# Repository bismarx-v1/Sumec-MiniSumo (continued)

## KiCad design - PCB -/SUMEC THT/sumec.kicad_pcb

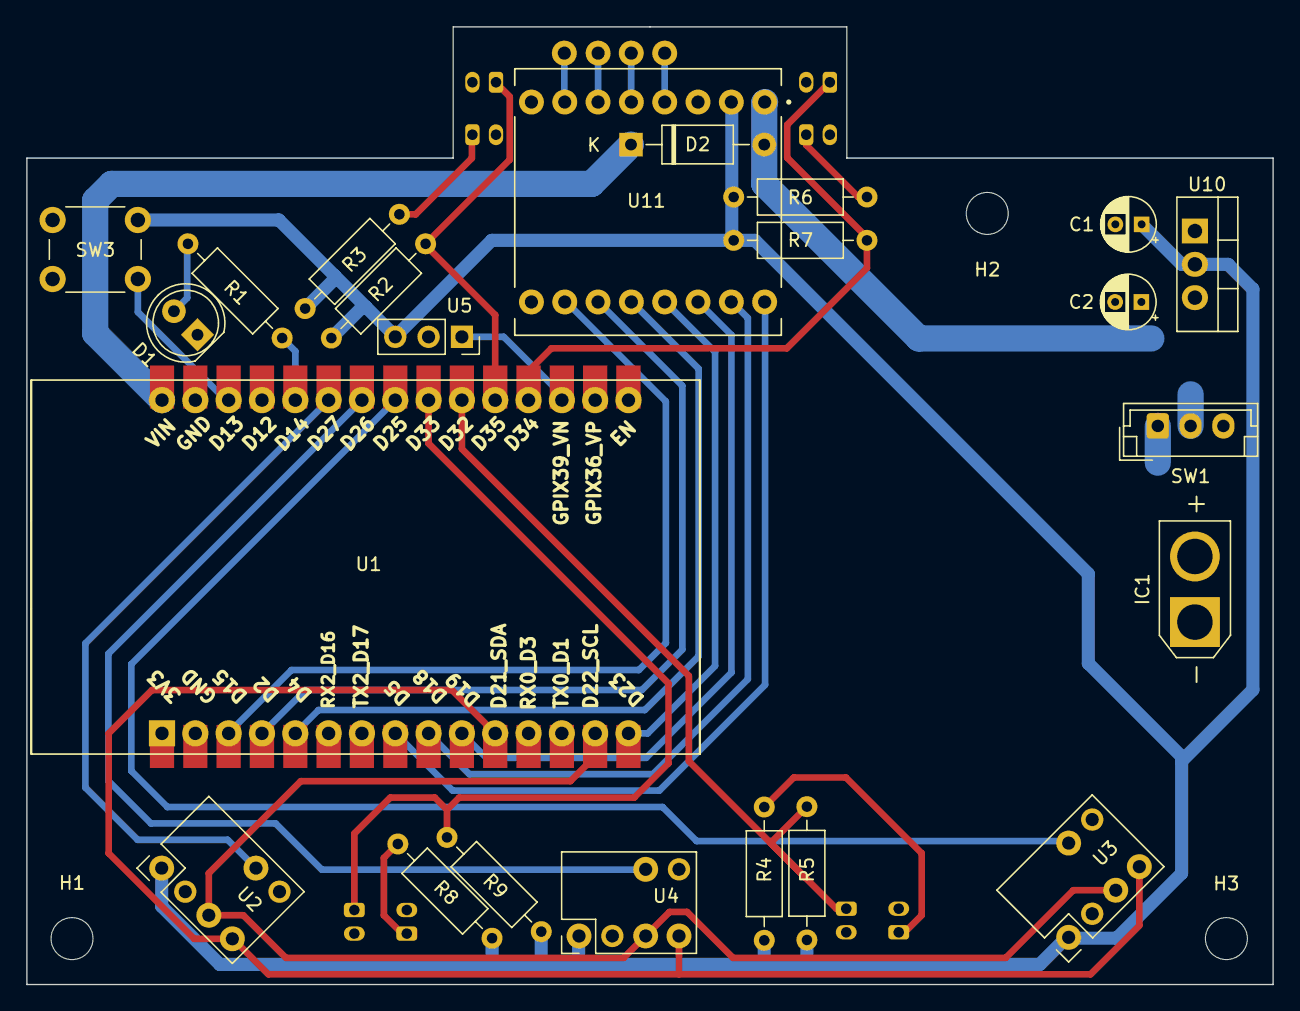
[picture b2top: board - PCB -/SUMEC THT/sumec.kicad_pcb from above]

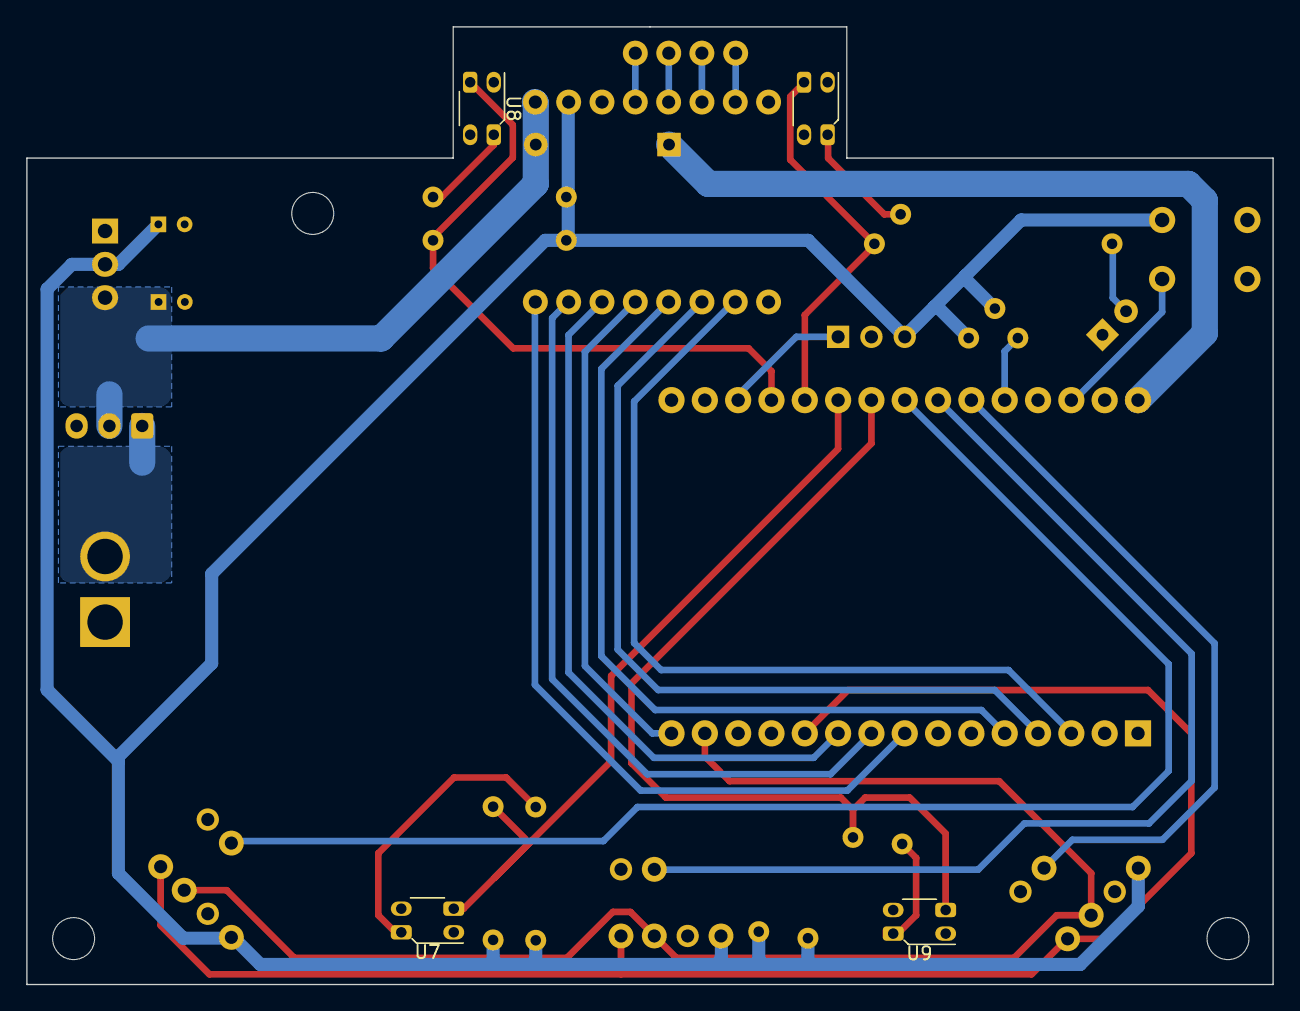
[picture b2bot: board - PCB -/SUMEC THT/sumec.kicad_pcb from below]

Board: 2 copper layers, 95.0 x 73.0 mm, 34 parts (4 on the bottom side), 33 nets.

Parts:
C1, C2: 10uF; CP_Radial_D4.0mm_P2.00mm
D1: RLED; LED_D5.0mm
D2: D_Schottky; D_A-405_P10.16mm_Horizontal
H1, H2, H3: MountingHole M3; MountingHole_3.2mm_M3
IC1: XT30U-F; AMASS_XT30U-M_1x02_P5.0mm_Vertical
J1, J2, J3, J4: Conn_01x01_Pin; SolderWire-0.5sqmm_1x01_D0.9mm_OD2.3mm
R1: 75; R_Axial_DIN0207_L6.3mm_D2.5mm_P10.16mm_Horizontal
R2, R4, R6, R8: 100; R_Axial_DIN0207_L6.3mm_D2.5mm_P10.16mm_Horizontal
R3, R5, R7, R9: 10k; R_Axial_DIN0207_L6.3mm_D2.5mm_P10.16mm_Horizontal
SW1: SW_SPDT; JST_EH_B3B-EH-A_1x03_P2.50mm_Vertical
SW3: SW_Push; SW_PUSH_6mm
U1: ESP32-DEVKIT-V1; MODULE_ESP32_DEVKIT_V1 B_Cu - PADS and no mount holes
U2, U3, U4: VL53L0X; GY-530 VL53L0X
U5: TSOP382xx; PinSocket_1x03_P2.54mm_Vertical
U6, U7, U8, U9: QRE1113; OnSemi_CASE100AQ - QRE1113
U10: LD1117AV33; TO-220-3_Vertical
U11: ROB-14450; ROB-14450 - TB6612FNG (MOTOR DRIVER)

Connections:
12V IN: IC1.2, SW1.1 (A)
+3V3: C1.1, R2.2, R3.1, R4.2, R5.1, R6.2, R7.1, R8.2, R9.1, SW3.1, U2.1 (VIN), U3.1 (VIN), U4.1 (VIN), U5.3 (Vs), U10.2 (OUT), U11.2 (VCC)
+12V: C2.1, D2.2 (A), SW1.2 (B), U10.3 (IN), U11.1 (VM)
AI1: U1.10 (D19), U11.14 (AI1)
AI2: U1.9 (D18), U11.15 (AI2)
BI1: U1.5 (D4), U11.12 (BI1)
BI2: U1.4 (D2), U11.11 (BI2)
GND: C1.2, C2.2, D1.1 (K), IC1.1, U1.2 (GND), U1.29 (GND), U2.2 (GND), U3.2 (GND), U4.2 (GND), U5.2 (GND), U6.2 (K), U6.4, U7.2 (K), U7.4, U8.2 (K), U8.4, U9.2 (K), U9.4, U10.1 (ADJ/GND), U11.3 (GND), U11.8 (GND), U11.9 (GND)
IR MODULE: U1.18 (GPIX39_VN), U5.1 (OUT)
LED SIGNALISATION: R1.2, U1.26 (D14)
MOTOR 1 +: J1.1, U11.4 (A01)
MOTOR 1 -: J2.1, U11.5 (A02)
MOTOR 2 +: J4.1, U11.6 (B02)
MOTOR 2 -: J3.1, U11.7 (B01)
unnamed: D1.2 (A), R1.1
unnamed: D2.1 (K), U1.30 (VIN)
unnamed: R2.1, U6.1 (A)
unnamed: R4.1, U7.1 (A)
unnamed: R6.1, U8.1 (A)
unnamed: R8.1, U9.1 (A)
PWMA: U1.8 (D5), U11.16 (PWMA)
PWMB: U1.3 (D15), U11.10 (PWMB)
QRE1113 A: R3.2, U1.20 (D35), U6.3
QRE1113 B: R5.2, U1.21 (D32), U7.3
QRE1113 C: R7.2, U1.19 (D34), U8.3
QRE1113 D: R9.2, U1.22 (D33), U9.3
SCL: U1.14 (D22_SCL), U2.3 (SCL), U3.3 (SCL), U4.3 (SCL)
SDA: U1.11 (D21_SDA), U2.4 (SDA), U3.4 (SDA), U4.4 (SDA)
STBY: U1.15 (D23), U11.13 (STBY)
TEST PROGRAM: SW3.2, U1.28 (D13)
X-SHUT 1: U1.25 (D27), U2.6 (XSHUT)
X-SHUT 2: U1.23 (D25), U3.6 (XSHUT)
X-SHUT 3: U1.24 (D26), U4.6 (XSHUT)

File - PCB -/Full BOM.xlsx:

| QTY | VALUE | COMPONENT | COST | DO WE HAVE IT?
 | 2 | 10uF | Cappacitor |  | 9
 | 1 | RED | LED | 0 | YES
 | 1 | D_Schottky | Diode |  | 2
 | 3 | M3 | Mounting Hole |  | 30
 | 1 | XT30U-F | Battery conneector |  | 2F and 2M
 | 1 | 75 | Resistor
 | 4 | 100 | Resistor |  | 6
 | 4 | 10k | Resistor |  | 10
 | 1 | SW_SPDT | Switch (3 pin header) |  | 2 types 8 in total
 | 1 | SW_Push | Button | 0 | YES
 | 1 | ESP32-DEVKIT-V1 | MCU |  | 3
 | 3 | VL53L0X | Laser Sensor |  | 4
 | 1 | TSOP382xx | IR Sensor |  | 1 module,
 | 4 | QRE1113 | Line Rensor |  | 10 smd 11 thd
 | 1 | LD1117AV33 | Stabiliastor |  | 2
 | 1 | ROB-14450 | Motor Driver |  | 4+1
 | 15x2 | 2,54mm | Pin Header
 | 8x2 | 2,54mm | Pin Header
 | 3 | CUSTOM MADE | Laser sensor connector
 | 2 | 12V 150/300/500 RPM | DC Motors |  | 8
 | 1 | 450mAh, 12,6V full charge | Battery/Terrorist battery |  | 1+1
 | 2 | JSUMO | Silicon wheels |  | 3
 | 2 | JSUMO/Custom made | Aluminuim wheels |  | 2+2
 | 1 | Tester | Battery Tester |  | 1

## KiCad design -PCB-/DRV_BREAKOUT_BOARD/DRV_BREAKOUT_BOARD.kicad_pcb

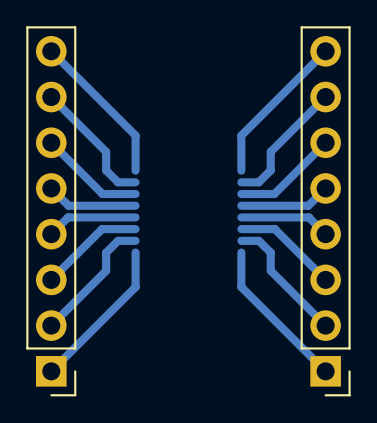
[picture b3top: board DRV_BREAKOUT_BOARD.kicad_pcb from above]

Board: 2 copper layers, 3 parts (1 on the bottom side), 16 nets.

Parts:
IC1: DRV8874PWPR; DRV8874
J1, J2: Conn_01x08_Pin; PinHeader_1x08_P2.54mm_Vertical

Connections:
unnamed: IC1.13 (CPH), J1.4
unnamed: IC1.14 (CPL), J1.3
unnamed: IC1.1 (EN/IN1), J2.1
unnamed: IC1.15 (GND), J1.2
unnamed: IC1.7 (IMODE), J2.7
unnamed: IC1.6 (IPROPI), J2.6
unnamed: IC1.4 (NFAULT), J2.4
unnamed: IC1.3 (NSLEEP), J2.3
unnamed: IC1.8 (OUT1), J2.8
unnamed: IC1.10 (OUT2), J1.7
unnamed: IC1.9 (PGND), J1.8
unnamed: IC1.2 (PH/IN2), J2.2
unnamed: IC1.16 (PMODE), J1.1
unnamed: IC1.12 (VCP), J1.5
unnamed: IC1.11 (VM), J1.6
unnamed: IC1.5 (VREF), J2.5

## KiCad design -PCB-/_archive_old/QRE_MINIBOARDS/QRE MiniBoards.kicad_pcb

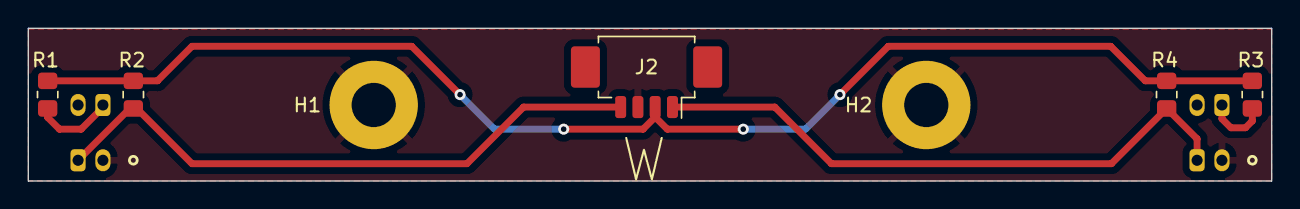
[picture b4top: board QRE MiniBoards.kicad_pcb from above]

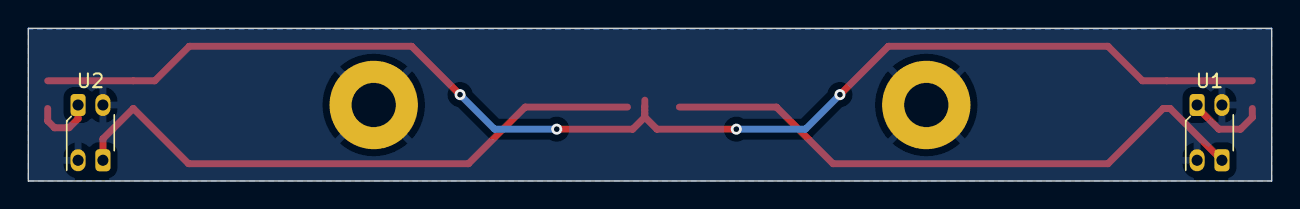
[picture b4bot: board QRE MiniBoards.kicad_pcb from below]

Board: 2 copper layers, 90.0 x 11.0 mm, 9 parts (2 on the bottom side), 6 nets.

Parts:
H1, H2: M3; MountingHole_3.2mm_M3_Pad
J2: Conn_01x04_Pin; Molex_PicoBlade_53261-0471_1x04-1MP_P1.25mm_Horizontal
R1, R3: 100; R_0805_2012Metric_Pad1.20x1.40mm_HandSolder
R2, R4: 10k; R_0805_2012Metric_Pad1.20x1.40mm_HandSolder
U1, U2: QRE1113; OnSemi_CASE100AQ - QRE1113

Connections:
+3V3: J2.2, R1.2, R2.1, R3.2, R4.1
GND: H1.1, H2.1, J2.3, U1.2 (K), U1.4, U2.2 (K), U2.4
unnamed: R1.1, U1.1 (A)
unnamed: R3.1, U2.1 (A)
QRE1113 A: J2.4, R2.2, U1.3
QRE1113 B: J2.1, R4.2, U2.3

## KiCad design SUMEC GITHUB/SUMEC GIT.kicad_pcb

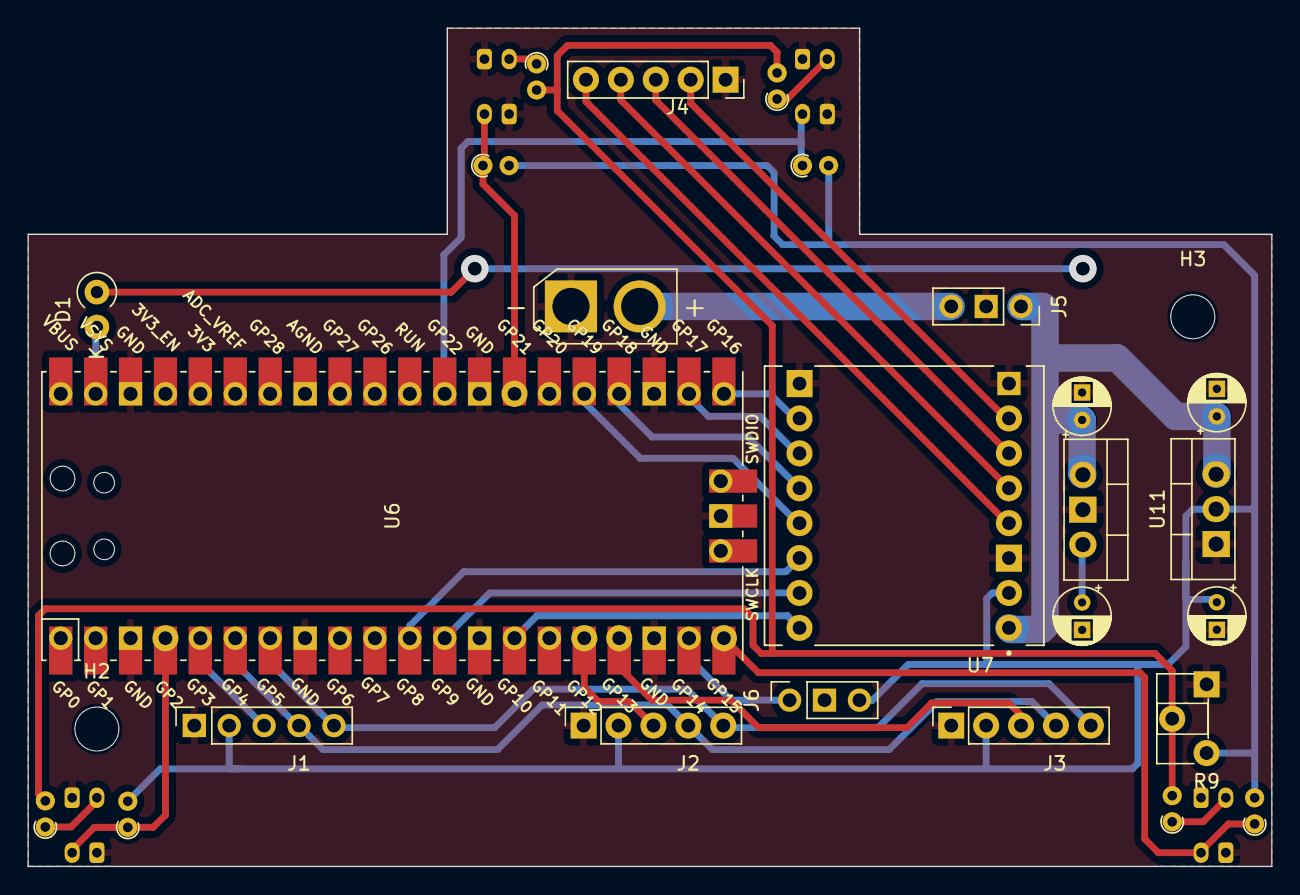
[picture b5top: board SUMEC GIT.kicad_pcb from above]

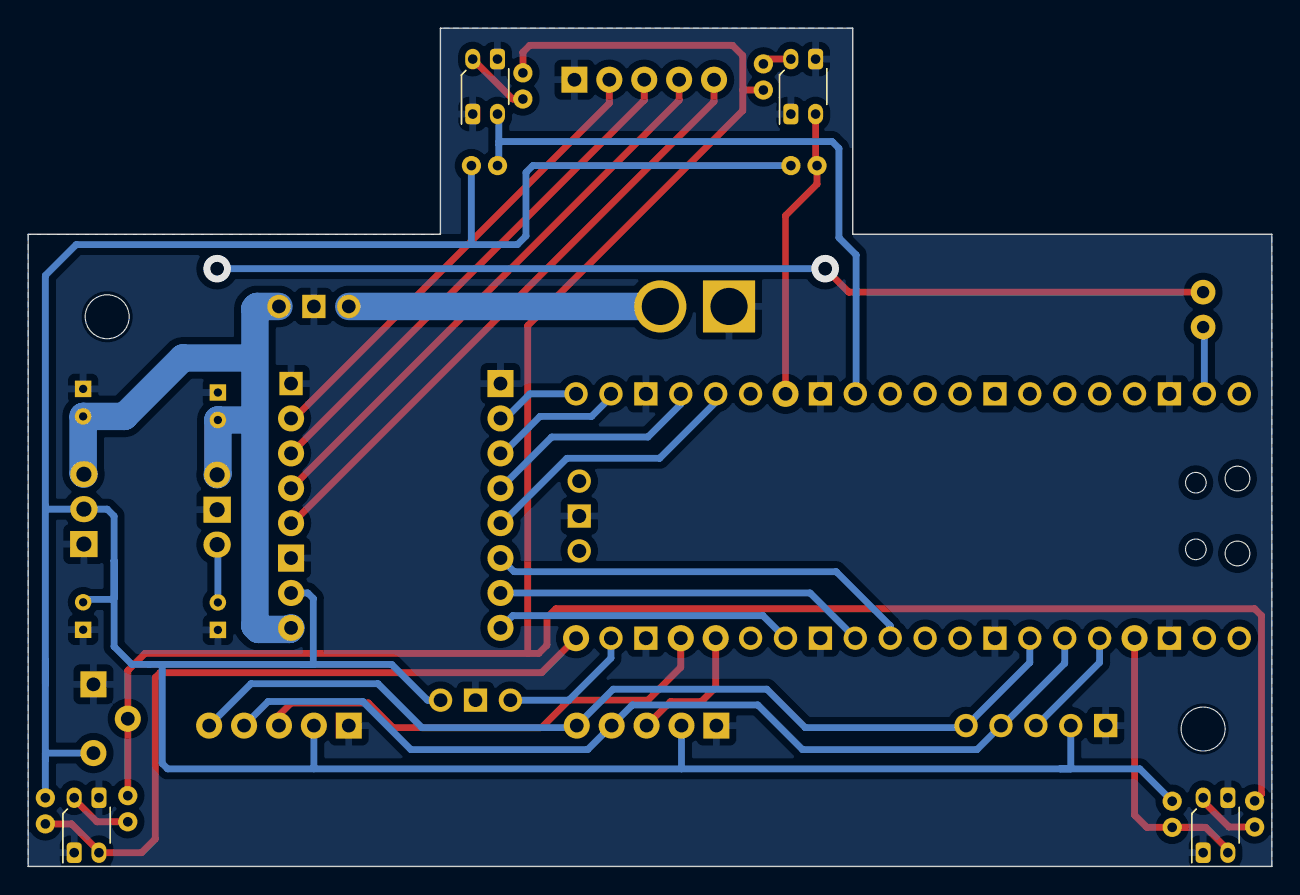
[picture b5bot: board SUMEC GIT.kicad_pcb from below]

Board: 2 copper layers, 90.5 x 61.0 mm, 31 parts (4 on the bottom side), 31 nets.

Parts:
C1: 0,1uF; CP_Radial_D4.0mm_P2.00mm
C2: 22uF; CP_Radial_D4.0mm_P2.00mm
C3, C4: 10uF; CP_Radial_D4.0mm_P2.00mm
D1: D_Schottky; D_A-405_P2.54mm_Vertical_KathodeUp
H2, H3: MountingHole M3; MountingHole_3.2mm_M3
IC1: XT30U-M; AMASS_XT30U-M_1x02_P5.0mm_Vertical
J1, J2, J3: Conn_01x05_Pin; PinSocket_1x05_P2.54mm_Vertical
J4: Conn_01x05_Male; PinSocket_1x05_P2.54mm_Vertical
J5, J6: Conn_01x03_Male; PinSocket_1x03_P2.54mm_Vertical
R1, R3, R5, R7: 100; R_Axial_DIN0204_L3.6mm_D1.6mm_P1.90mm_Vertical
R2, R4, R6, R8: 10k; R_Axial_DIN0204_L3.6mm_D1.6mm_P1.90mm_Vertical
R9: R_Trim; Potentiometer_ACP_CA6-H2,5_Horizontal
U1, U2, U3, U4: QRE1113; OnSemi_CASE100AQ
U6: Pico; RPi_Pico_SMD_TH
U7: ROB-14450; MODULE_ROB-14450
U11: LD1086V33-DG; TO-220-3_Vertical
U12: LM7805_TO220; TO-220-3_Vertical

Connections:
+3V3: C3.1, J1.2, J2.2, J3.2, J6.3, R2.2, R4.2, R6.2, R8.2, R9.1, U7.2 (VCC), U11.2 (OUT)
+5V: C2.1, D1.2 (A), U12.3 (VO)
+12V: C1.1, C4.1, IC1.2, J5.1, J5.3, U7.1 (VM), U11.3 (IN), U12.1 (VI)
AI1: U6.11 (GPIO8), U7.14 (AI1)
AI2: U6.12 (GPIO9), U7.15 (AI2)
BI1: U6.24 (GPIO18), U7.12 (BI1)
BI2: U6.22 (GPIO17), U7.11 (BI2)
GND: C1.2, C2.2, C3.2, C4.2, IC1.1, J1.1, J2.1, J3.1, J4.1, J5.2, J6.2, U1.2 (K), U1.4, U2.2 (K), U2.4, U3.2 (K), U3.4, U4.2 (K), U4.4, U6.3 (GND), U6.8 (GND), U6.13 (GND), U6.18 (GND), U6.23 (GND), U6.28 (GND), U6.38 (GND), U6.42 (GND), U7.3 (GND), U7.8 (GND), U7.9 (GND), U11.1 (ADJ/GND), U12.2 (GND)
IR MODULE: J6.1, U6.19 (GPIO14)
MOTOR 1 +: J4.5, U7.4 (A01)
MOTOR 1 -: J4.4, U7.5 (A02)
MOTOR 2 +: J4.3, U7.6 (B02)
MOTOR 2 -: J4.2, U7.7 (B01)
unnamed: D1.1 (K), U6.39 (VSYS)
unnamed: R1.2, R3.2, R5.2, R7.2, R9.2
unnamed: R1.1, U1.1 (A)
unnamed: R3.1, U2.1 (A)
unnamed: R5.1, U3.1 (A)
unnamed: R7.1, U4.1 (A)
PWMA: U6.14 (GPIO10), U7.16 (PWMA)
PWMB: U6.21 (GPIO16), U7.10 (PWMB)
QRE1113 A: R2.1, U1.3, U6.4 (GPIO2)
QRE1113 B: R4.1, U2.3, U6.20 (GPIO15)
QRE1113 C: R6.1, U3.3, U6.29 (GPIO22)
QRE1113 D: R8.1, U4.3, U6.27 (GPIO21)
SCL: J1.5, J2.5, J3.5, U6.7 (GPIO5)
SDA: J1.4, J2.4, J3.4, U6.6 (GPIO4)
STBY: U6.25 (GPIO19), U7.13 (STBY)
X-SHUT 1: J1.3, U6.5 (GPIO3)
X-SHUT 2: J2.3, U6.16 (GPIO12)
X-SHUT 3: J3.3, U6.17 (GPIO13)
